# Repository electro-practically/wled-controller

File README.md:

# WLED Controller

**WLED Controller** is a compact, **single-sided PCB** designed to run WLED firmware and control **two addressable LED strips**. It is powered entirely via **USB-C Power-Delivery** and supports either **5V or 12V** LED strips, with a maximum power of **60W**. Compatible with popular LED types such as **WS2812B** (5V) and **WS2815** (12V). It offers a clean, efficient solution for custom lighting projects.

## Block diagram

The entire board is powered via the USB-C connector. Voltage and current levels are negotiated through the TPS25730D USB Power Delivery (PD) controller, based on onboard configuration resistors. The supported input range is 5–20 V and 0.5–5 A, and the controller always negotiates the highest available voltage profile supported by the connected power adapter. These voltage/current profiles can be customized by soldering different resistor values.

There are two power paths:

1. **LED Power Path**: supplies power to the LED strips. The input voltage is stepped down by a SiC437 buck converter, providing high-efficiency regulation tailored to the selected LED voltage (5 V or 12 V). This path is protected by a fuse.

2. **Logic Power Path**: supplies power to the ESP32 and other low-power components. This path uses a TPS54202 buck converter to generate a stable 5 V rail, which is further regulated down to 3.3 V using an AMS1117 low-dropout (LDO) regulator.

A dedicated ENABLE signal from the ESP32 is used to control the LED power converter (SiC437). When LEDs are turned off in WLED, this signal disables the converter entirely - removing the need for additional output relays or transistors typically used to disconnect LED power.

The USB-C connector also provides a direct connection to the ESP32 via the USB 2.0, allowing firmware flashing and debug access without additional interfaces.

## PCB description

1. **USB-C connector.** Used for flashing the WLED firmware onto the ESP32 and for powering the entire board—including connected LED strips—via the USB Power Delivery (PD) protocol. Ensure you use a high-quality USB-C cable capable of handling the required current.
2. **LED output 1.** Connector for the first LED strip, providing power (+/-) and data signals.
3. **LED output 2.** Connector for the second LED strip, providing power (+/-) and data signals.
4. **LED voltage selector.** This 3-pin jumper is used to select the output voltage for the connected LED strips - either 5V or 12V. Always short the center pin with either the 5V or 12V pin, depending on your required LED strip voltage. Be careful, if no jumper is installed, the output voltage will be extremely low (close to 0V), and the LED strips will not function properly.
5. **Protection fuse.** Protects the board from short circuits or faults originating from the connected LED strips.
6. **GPIOs.** These exposed GPIO pins can be configured in WLED to support a variety of additional functions beyond basic LED control, including buttons, I2S microphone, IR receiver etc. Pin description:
    1. +5V
    2. +3.3V
    3. GPIO20
    4. GPIO21
    5. GPIO3
    6. GPIO4
    7. GPIO5
    8. GND
7. **Boot jumper.** Used to place the ESP32 into bootloader mode for firmware flashing.

## Bring-up guide

Follow these steps to flash the WLED firmware and configure the board:

1. Set the LED voltage jumper (5 V or 12 V) according to your connected LED strips.
2. Place a jumper on the BOOT connector to put the ESP32 into bootloader mode.
3. Connect the board to your PC using a USB-C cable.
4. Once connected, remove the BOOT jumper.
5. Install the WLED firmware following the official instructions: [kno.wled.ge](https://kno.wled.ge/basics/getting-started/)
6. Configure WLED as follows (see LED Preferences settings category in the web UI):
    1. **LED1 Data GPIO**: 7
    2. **LED2 Data GPIO**: 6
    3. **Relay GPIO**: 10 (no invert, no open drain)
7. Disconnect the USB from your PC and connect a suitable power adapter via USB-C.
8. Setup complete - the board is ready to use.

## Thermal consideration

If you power a long LED strip with relatively high power consumption, it may be necessary to provide heat dissipation for the controller - for example, using an aluminum case or a case with a fan. Most of the heat is dissipated by the SiC437 buck converter.

## Input power source type

The controller was tested with a standard USB power brick used for phone charging with USB Power Delivery capability. However, it should also work with other USB-C devices that support Power Delivery in source mode - for example, power banks, monitors, laptops, and similar devices. If you plan to power the controller from such a source, ensure that it supports the required USB PD power profile.

## License

[CERN Open Hardware Licence Version 2 - Permissive](https://cern-ohl.web.cern.ch/home)

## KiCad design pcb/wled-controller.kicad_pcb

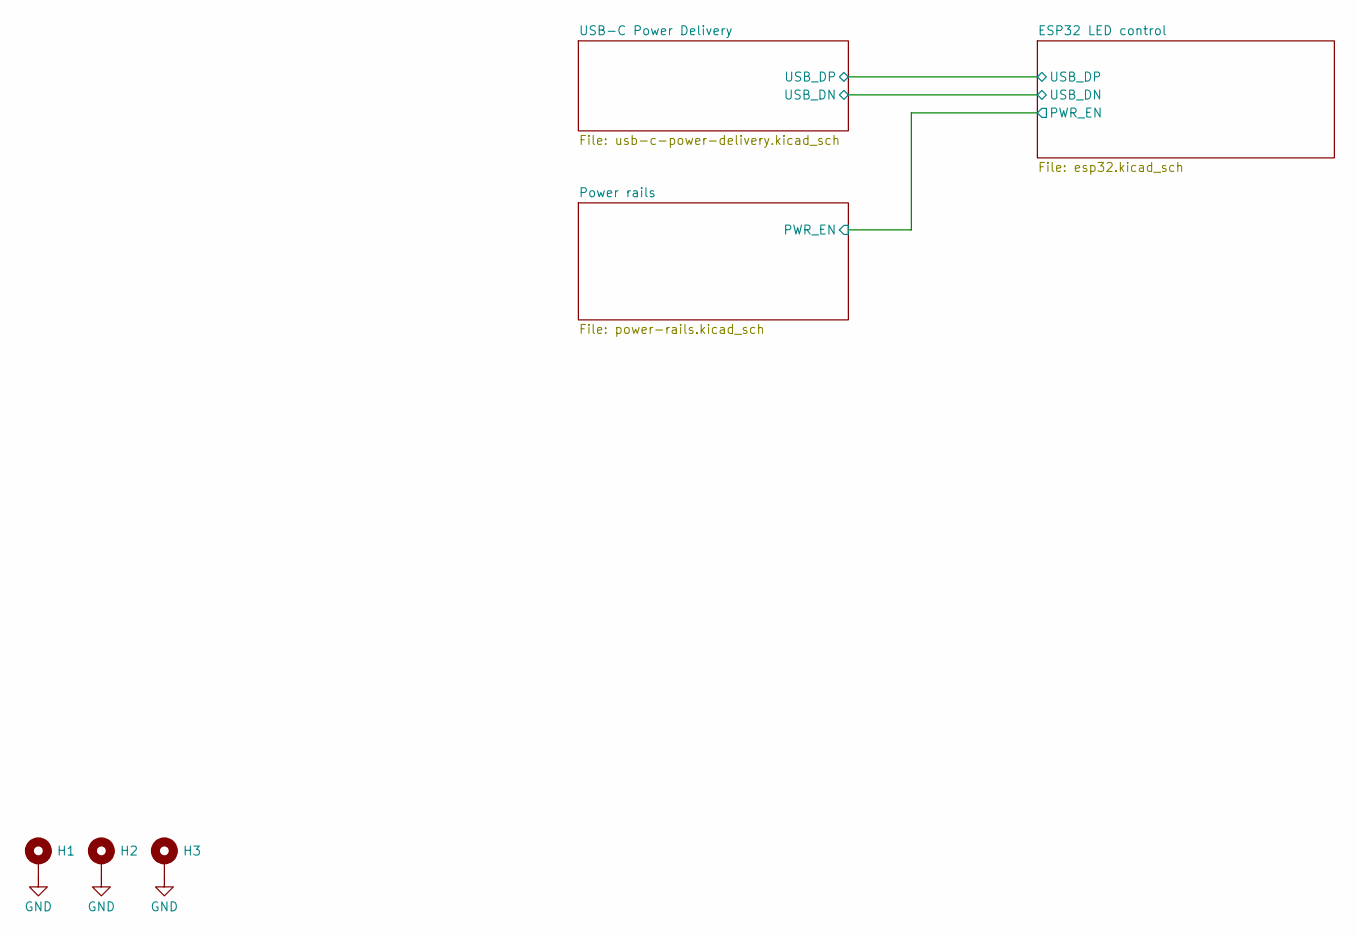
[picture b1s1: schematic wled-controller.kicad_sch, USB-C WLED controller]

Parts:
H1, H2, H3: MountingHole; MountingHole_3.2mm_M3_DIN965_Pad

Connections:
GND: H1.1, H2.1, H3.1; also elsewhere on the board

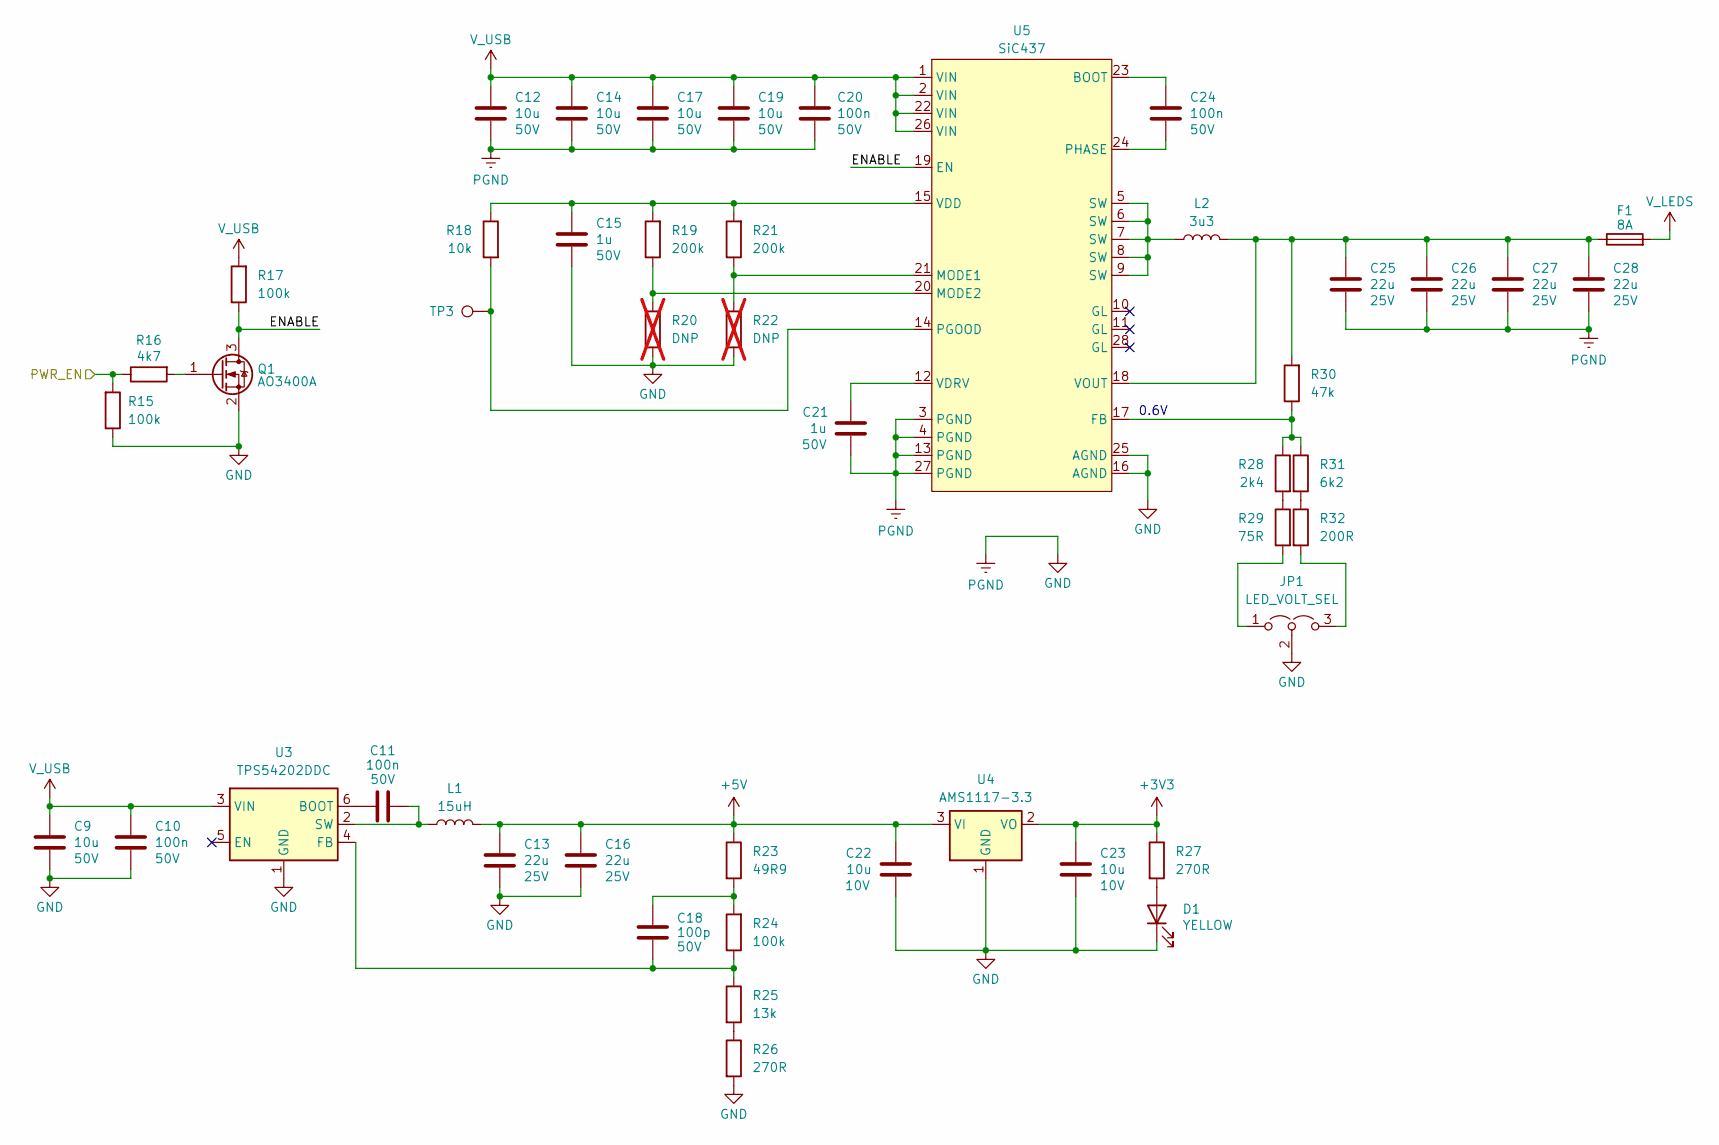
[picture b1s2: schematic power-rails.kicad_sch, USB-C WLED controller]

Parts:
C9, C12, C14, C17, C19: 10u; C_1206_3216Metric; Voltage 50V; JLCPCB C13585
C10, C11, C20, C24: 100n; C_0603_1608Metric; Voltage 50V; JLCPCB C14663
C13, C16, C25, C26, C27, C28: 22u; C_1206_3216Metric; Voltage 25V; JLCPCB C12891
C15, C21: 1u; C_0603_1608Metric; Voltage 50V; JLCPCB C15849
C18: 100p; C_0603_1608Metric; Voltage 50V; JLCPCB C14858
C22, C23: 10u; C_0603_1608Metric; Voltage 10V; JLCPCB C19702
D1: YELLOW; LED_0603_1608Metric; JLCPCB C72038
F1: 8A; Fuseholder_Littelfuse_Nano2_154x; JLCPCB C108518
JP1: LED_VOLT_SEL; PinHeader_1x03_P2.54mm_Vertical; JLCPCB C2937625
L1: 15uH; L_Changjiang_FNR4020S; JLCPCB C167837
L2: 3u3; L_Chilisin_BMRF00101040; JLCPCB C7587741
Q1: AO3400A; SOT-23; JLCPCB C20917
R15, R17, R24: 100k; R_0603_1608Metric; JLCPCB C25803
R16: 4k7; R_0603_1608Metric; JLCPCB C23162
R18: 10k; R_0603_1608Metric; JLCPCB C25804
R19, R21: 200k; R_0603_1608Metric; JLCPCB C25811
R20, R22: DNP; R_0603_1608Metric; not fitted
R23: 49R9; R_0603_1608Metric; JLCPCB C23185
R25: 13k; R_0603_1608Metric; JLCPCB C22797
R26, R27: 270R; R_0603_1608Metric; JLCPCB C22966
R28: 2k4; R_0603_1608Metric; JLCPCB C22940
R29: 75R; R_0603_1608Metric; JLCPCB C4275
R30: 47k; R_0603_1608Metric; JLCPCB C25819
R31: 6k2; R_0603_1608Metric; JLCPCB C4260
R32: 200R; R_0603_1608Metric; JLCPCB C8218
TP3: TESTPOINT; TestPoint_Pad_D1.0mm
U3: TPS54202DDC; SOT-23-6; JLCPCB C191884
U4: AMS1117-3.3; SOT-223-3_TabPin2; JLCPCB C6186
U5: SiC437; SIC437BEDT1GE3; JLCPCB C2071432

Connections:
+3V3: C23.1, R27.1, U4.2 (VO); also elsewhere on the board
+5V: C13.1, C16.1, C22.1, L1.2, R23.1, U4.3 (VI); also elsewhere on the board
/ESP32 LED control/PWR_EN: R15.2, R16.1; also elsewhere on the board
/Power rails/ENABLE: Q1.3 (D), R17.1, U5.19 (EN)
GND: C9.2, C10.1, C12.2, C13.2, C14.2, C15.1, C16.2, C17.2, C19.2, C20.2, C21.1, C22.2, C23.2, C25.2, C26.2, C27.2, C28.2, D1.1 (K), JP1.2 (C), Q1.2 (S), R15.1, R20.1, R22.1, R26.2, U3.1 (GND), U4.1 (GND), U5.3 (PGND), U5.4 (PGND), U5.13 (PGND), U5.16 (AGND), U5.25 (AGND), U5.27 (PGND); also elsewhere on the board
unnamed: C18.1, R23.2, R24.2
unnamed: D1.2 (A), R27.2
unnamed: JP1.1 (A), R29.2
unnamed: JP1.3 (B), R32.2
unnamed: L2.1, U5.5 (SW), U5.6 (SW), U5.7 (SW), U5.8 (SW), U5.9 (SW)
unnamed: Q1.1 (G), R16.2
unnamed: R25.2, R26.1
unnamed: R28.2, R29.1
unnamed: R31.2, R32.1
unnamed: C11.2, U3.6 (BOOT)
unnamed: C18.2, R24.1, R25.1, U3.4 (FB)
unnamed: C11.1, L1.1, U3.2 (SW)
unnamed: C24.2, U5.23 (BOOT)
unnamed: R28.1, R30.1, R31.1, U5.17 (FB)
unnamed: R21.1, R22.2, U5.21 (MODE1)
unnamed: R19.1, R20.2, U5.20 (MODE2)
unnamed: R18.2, TP3.1, U5.14 (PGOOD)
unnamed: C24.1, U5.24 (PHASE)
unnamed: C15.2, R18.1, R19.2, R21.2, U5.15 (VDD)
unnamed: C21.2, U5.12 (VDRV)
unnamed: C25.1, C26.1, C27.1, C28.1, F1.1, L2.2, R30.2, U5.18 (VOUT)
V_LEDS: F1.2; also elsewhere on the board
V_USB: C9.1, C10.2, C12.1, C14.1, C17.1, C19.1, C20.1, R17.2, U3.3 (VIN), U5.1 (VIN), U5.2 (VIN), U5.22 (VIN), U5.26 (VIN); also elsewhere on the board

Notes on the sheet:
0.6V

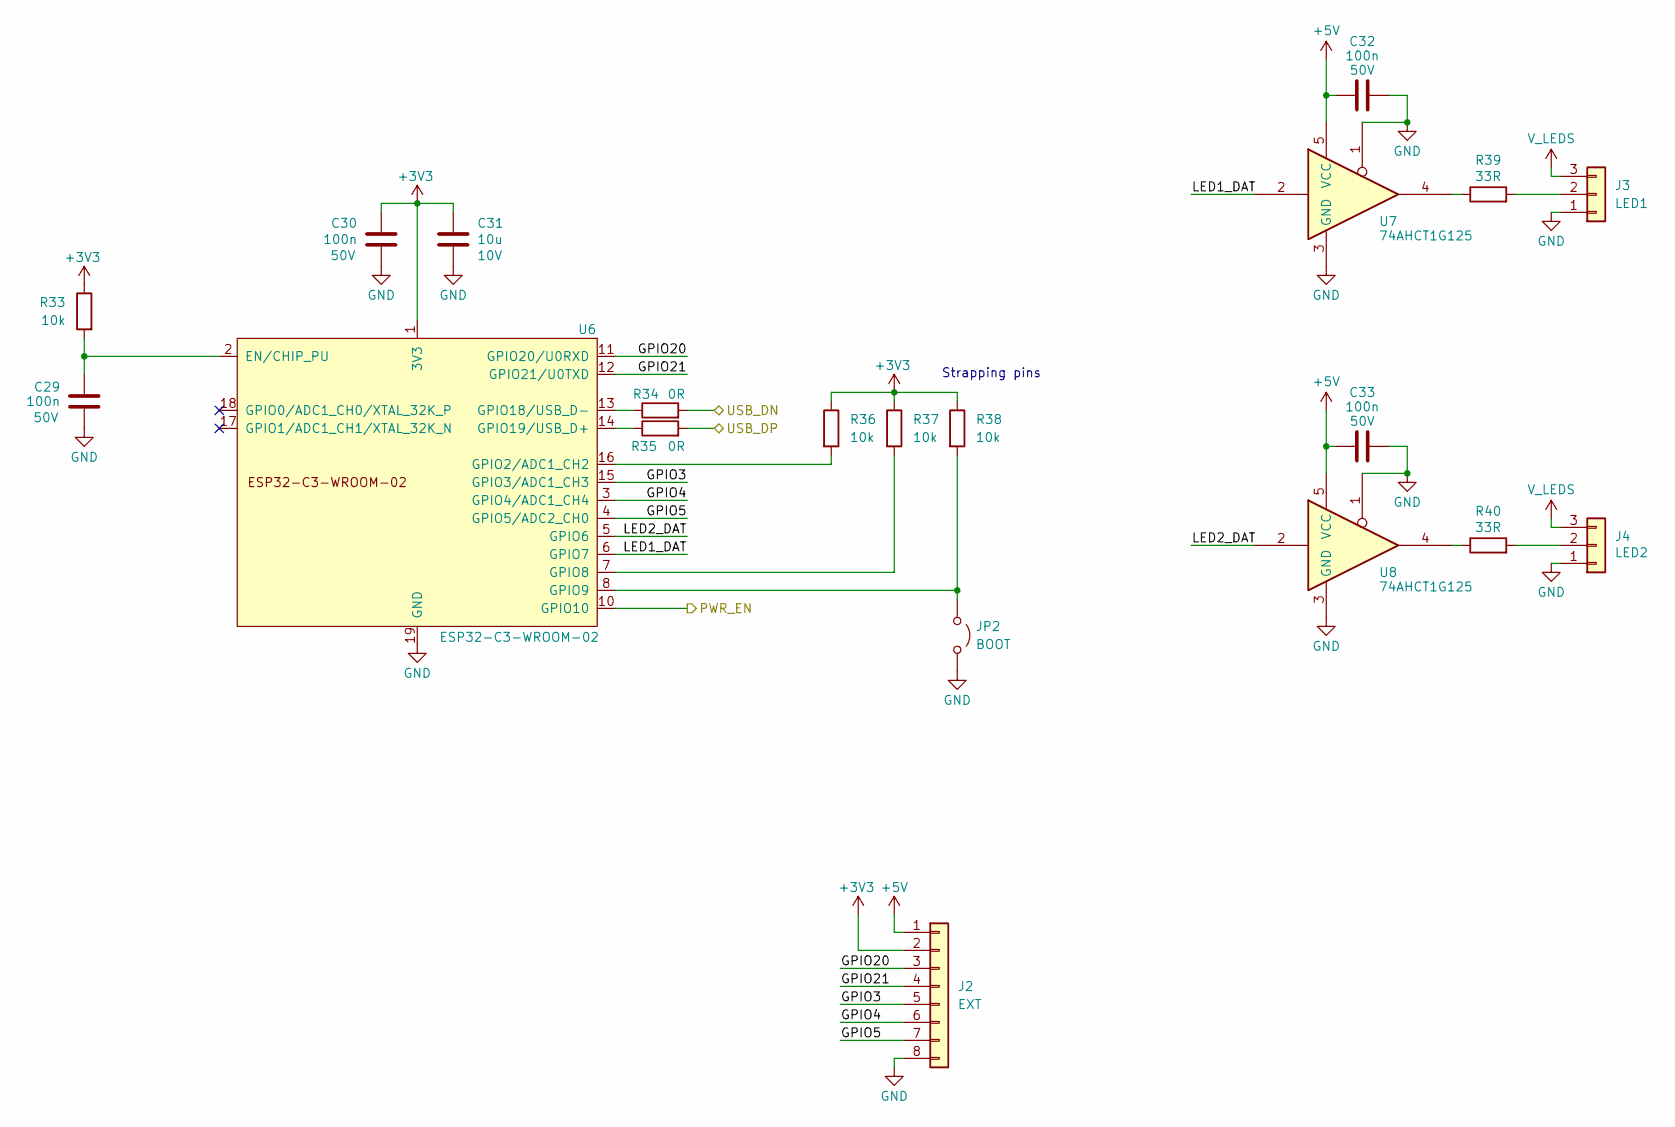
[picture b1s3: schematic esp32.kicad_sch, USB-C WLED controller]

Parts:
C29, C30, C32, C33: 100n; C_0603_1608Metric; Voltage 50V; JLCPCB C14663
C31: 10u; C_0603_1608Metric; Voltage 10V; JLCPCB C19702
J2: EXT; PinHeader_1x08_P2.54mm_Vertical
J3: LED1; PhoenixContact_MSTBA_2,5_3-G-5,08_1x03_P5.08mm_Horizontal; JLCPCB C8377
J4: LED2; PhoenixContact_MSTBA_2,5_3-G-5,08_1x03_P5.08mm_Horizontal; JLCPCB C8377
JP2: BOOT; PinHeader_1x02_P2.54mm_Vertical; JLCPCB C492401
R33, R36, R37, R38: 10k; R_0603_1608Metric; JLCPCB C25804
R34, R35: 0R; R_0603_1608Metric; JLCPCB C23162
R39, R40: 33R; R_0603_1608Metric; JLCPCB C23140
U6: ESP32-C3-WROOM-02; JLCPCB C2934560
U7, U8: 74AHCT1G125; SOT-353_SC-70-5; JLCPCB C151417

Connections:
+3V3: C30.1, C31.1, J2.2, R33.1, R36.1, R37.1, R38.1, U6.1 (3V3); also elsewhere on the board
+5V: C32.1, C33.1, J2.1, U7.5 (VCC), U8.5 (VCC); also elsewhere on the board
/ESP32 LED control/GPIO3: J2.5, U6.15 (GPIO3/ADC1_CH3)
/ESP32 LED control/GPIO4: J2.6, U6.3 (GPIO4/ADC1_CH4)
/ESP32 LED control/GPIO5: J2.7, U6.4 (GPIO5/ADC2_CH0)
/ESP32 LED control/GPIO20: J2.3, U6.11 (GPIO20/U0RXD)
/ESP32 LED control/GPIO21: J2.4, U6.12 (GPIO21/U0TXD)
/ESP32 LED control/LED1_DAT: U6.6 (GPIO7), U7.2
/ESP32 LED control/LED2_DAT: U6.5 (GPIO6), U8.2
/ESP32 LED control/PWR_EN: U6.10 (GPIO10); also elsewhere on the board
/ESP32 LED control/USB_DN: R34.2; also elsewhere on the board
/ESP32 LED control/USB_DP: R35.2; also elsewhere on the board
GND: C29.2, C30.2, C31.2, C32.2, C33.2, J2.8, J3.1, J4.1, JP2.2 (B), U6.9 (GND), U6.19 (GND), U7.1, U7.3 (GND), U8.1, U8.3 (GND); also elsewhere on the board
unnamed: J3.2, R39.2
unnamed: J4.2, R40.2
unnamed: JP2.1 (A), R38.2, U6.8 (GPIO9)
unnamed: R39.1, U7.4
unnamed: R40.1, U8.4
unnamed: C29.1, R33.2, U6.2 (EN/CHIP_PU)
unnamed: R36.2, U6.16 (GPIO2/ADC1_CH2)
unnamed: R37.2, U6.7 (GPIO8)
unnamed: R34.1, U6.13 (GPIO18/USB_D-)
unnamed: R35.1, U6.14 (GPIO19/USB_D+)
V_LEDS: J3.3, J4.3; also elsewhere on the board

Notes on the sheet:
Strapping pins

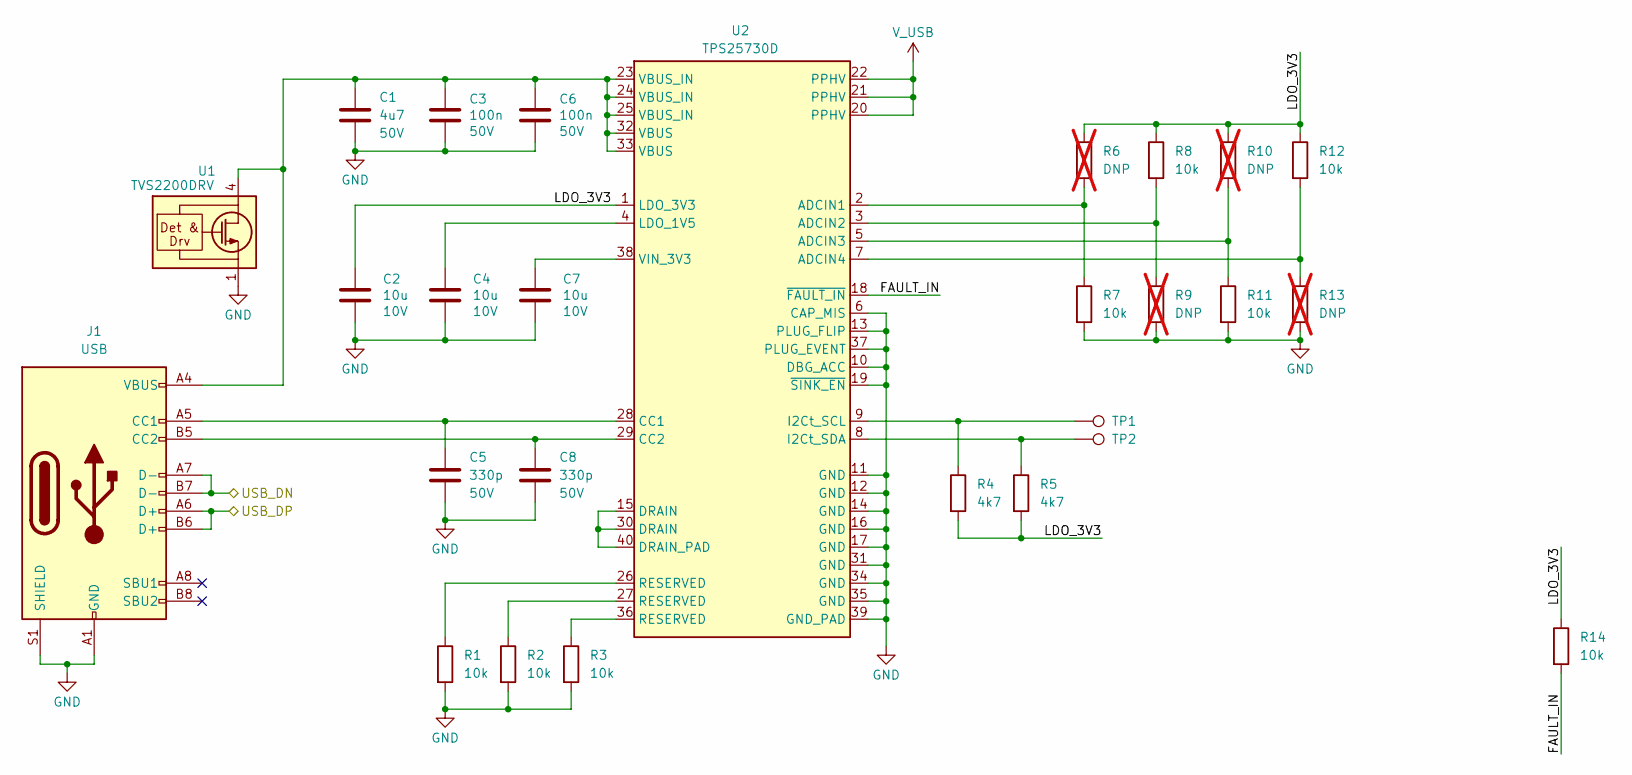
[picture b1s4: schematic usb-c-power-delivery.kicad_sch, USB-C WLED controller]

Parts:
C1: 4u7; C_1206_3216Metric; Voltage 50V; JLCPCB C29823
C2, C4, C7: 10u; C_0603_1608Metric; Voltage 10V; JLCPCB C19702
C3, C6: 100n; C_0603_1608Metric; Voltage 50V; JLCPCB C14663
C5, C8: 330p; C_0603_1608Metric; Voltage 50V; JLCPCB C1664
J1: USB; USB_C_Receptacle_XKB_U262-16XN-4BVC11; JLCPCB C165948
R1, R2, R3, R7, R8, R11, R12, R14: 10k; R_0603_1608Metric; JLCPCB C25804
R4, R5: 4k7; R_0603_1608Metric; JLCPCB C23162
R6, R9, R10, R13: DNP; R_0603_1608Metric; not fitted
TP1, TP2: TESTPOINT; TestPoint_Pad_D1.0mm
U1: TVS2200DRV; WSON-6-1EP_2x2mm_P0.65mm_EP1x1.6mm; JLCPCB C523793
U2: TPS25730D; IC_TPS25750DRJKR; JLCPCB C22438973

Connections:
/ESP32 LED control/USB_DN: J1.A7 (D-), J1.B7 (D-); also elsewhere on the board
/ESP32 LED control/USB_DP: J1.A6 (D+), J1.B6 (D+); also elsewhere on the board
/USB-C Power Delivery/FAULT_IN: R14.2, U2.18 (~FAULT_IN)
/USB-C Power Delivery/LDO_3V3: C2.1, R4.2, R5.2, R6.1, R8.1, R10.1, R12.1, R14.1, U2.1 (LDO_3V3)
GND: C1.2, C2.2, C3.2, C4.2, C5.2, C6.2, C7.2, C8.2, J1.A1 (GND), J1.A12 (GND), J1.B1 (GND), J1.B12 (GND), J1.S1 (SHIELD), R1.2, R2.2, R3.2, R7.2, R9.2, R11.2, R13.2, U1.1 (GND), U1.2 (GND), U1.3 (GND), U1.7 (GND), U2.6 (CAP_MIS), U2.10 (DBG_ACC), U2.11 (GND), U2.12 (GND), U2.13 (PLUG_FLIP), U2.14 (GND), U2.16 (GND), U2.17 (GND), U2.19 (~SINK_EN), U2.31 (GND), U2.34 (GND), U2.35 (GND), U2.37 (PLUG_EVENT), U2.39 (GND_PAD); also elsewhere on the board
unnamed: C1.1, C3.1, C6.1, J1.A4 (VBUS), J1.A9 (VBUS), J1.B4 (VBUS), J1.B9 (VBUS), U1.4 (IN), U1.5 (IN), U1.6 (IN), U2.23 (VBUS_IN), U2.24 (VBUS_IN), U2.25 (VBUS_IN), U2.32 (VBUS), U2.33 (VBUS)
unnamed: C5.1, J1.A5 (CC1), U2.28 (CC1)
unnamed: C8.1, J1.B5 (CC2), U2.29 (CC2)
unnamed: R1.1, U2.26 (RESERVED)
unnamed: R2.1, U2.27 (RESERVED)
unnamed: R3.1, U2.36 (RESERVED)
unnamed: R6.2, R7.1, U2.2 (ADCIN1)
unnamed: R8.2, R9.1, U2.3 (ADCIN2)
unnamed: R10.2, R11.1, U2.5 (ADCIN3)
unnamed: R12.2, R13.1, U2.7 (ADCIN4)
unnamed: U2.15 (DRAIN), U2.30 (DRAIN), U2.40 (DRAIN_PAD)
unnamed: R4.1, TP1.1, U2.9 (I2Ct_SCL)
unnamed: R5.1, TP2.1, U2.8 (I2Ct_SDA)
unnamed: C4.1, U2.4 (LDO_1V5)
unnamed: C7.1, U2.38 (VIN_3V3)
V_USB: U2.20 (PPHV), U2.21 (PPHV), U2.22 (PPHV); also elsewhere on the board

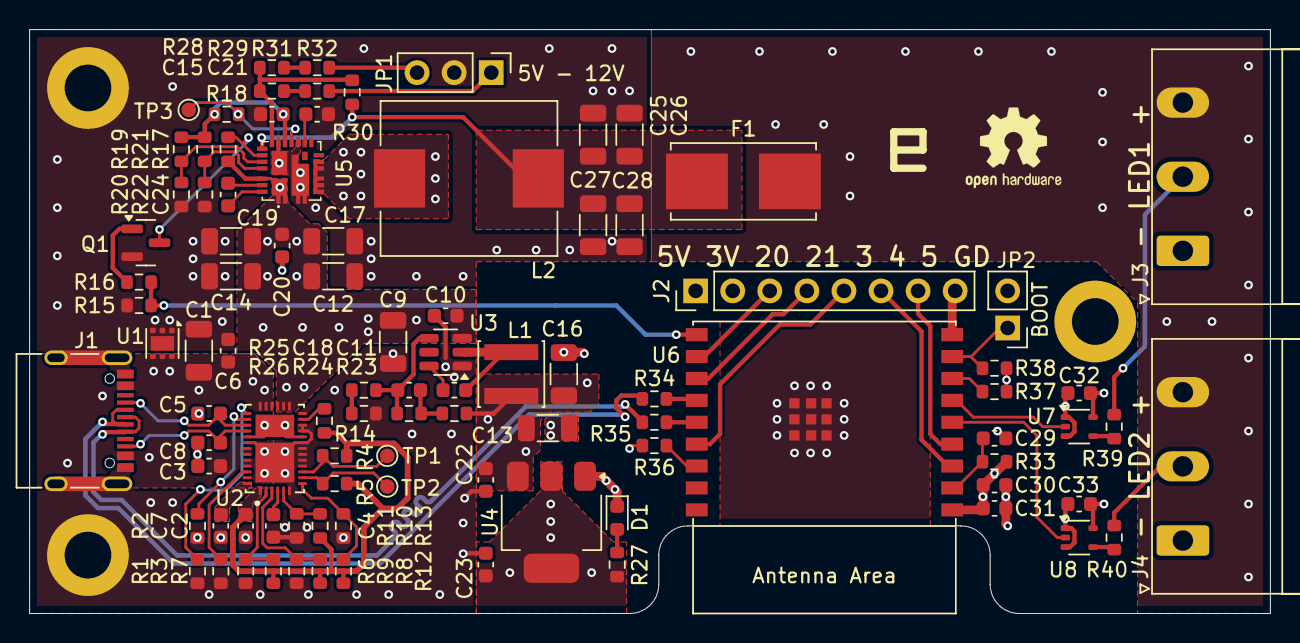
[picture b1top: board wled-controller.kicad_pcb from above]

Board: 4 copper layers, 85.0 x 40.0 mm, 98 parts (0 on the bottom side), 64 nets.

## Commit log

2025-06-14 Add project files
2025-06-15 Move PCB files to the parent directory
2025-06-18 Add case STL files for 3D printing
2025-06-18 Write README.md documentation.
2025-06-18 Add schematic as PDF.
2025-06-18 Fix images size in the README.md
2025-07-05 Fix link visibility in README.md
2025-07-05 Fix broken link in README.md
